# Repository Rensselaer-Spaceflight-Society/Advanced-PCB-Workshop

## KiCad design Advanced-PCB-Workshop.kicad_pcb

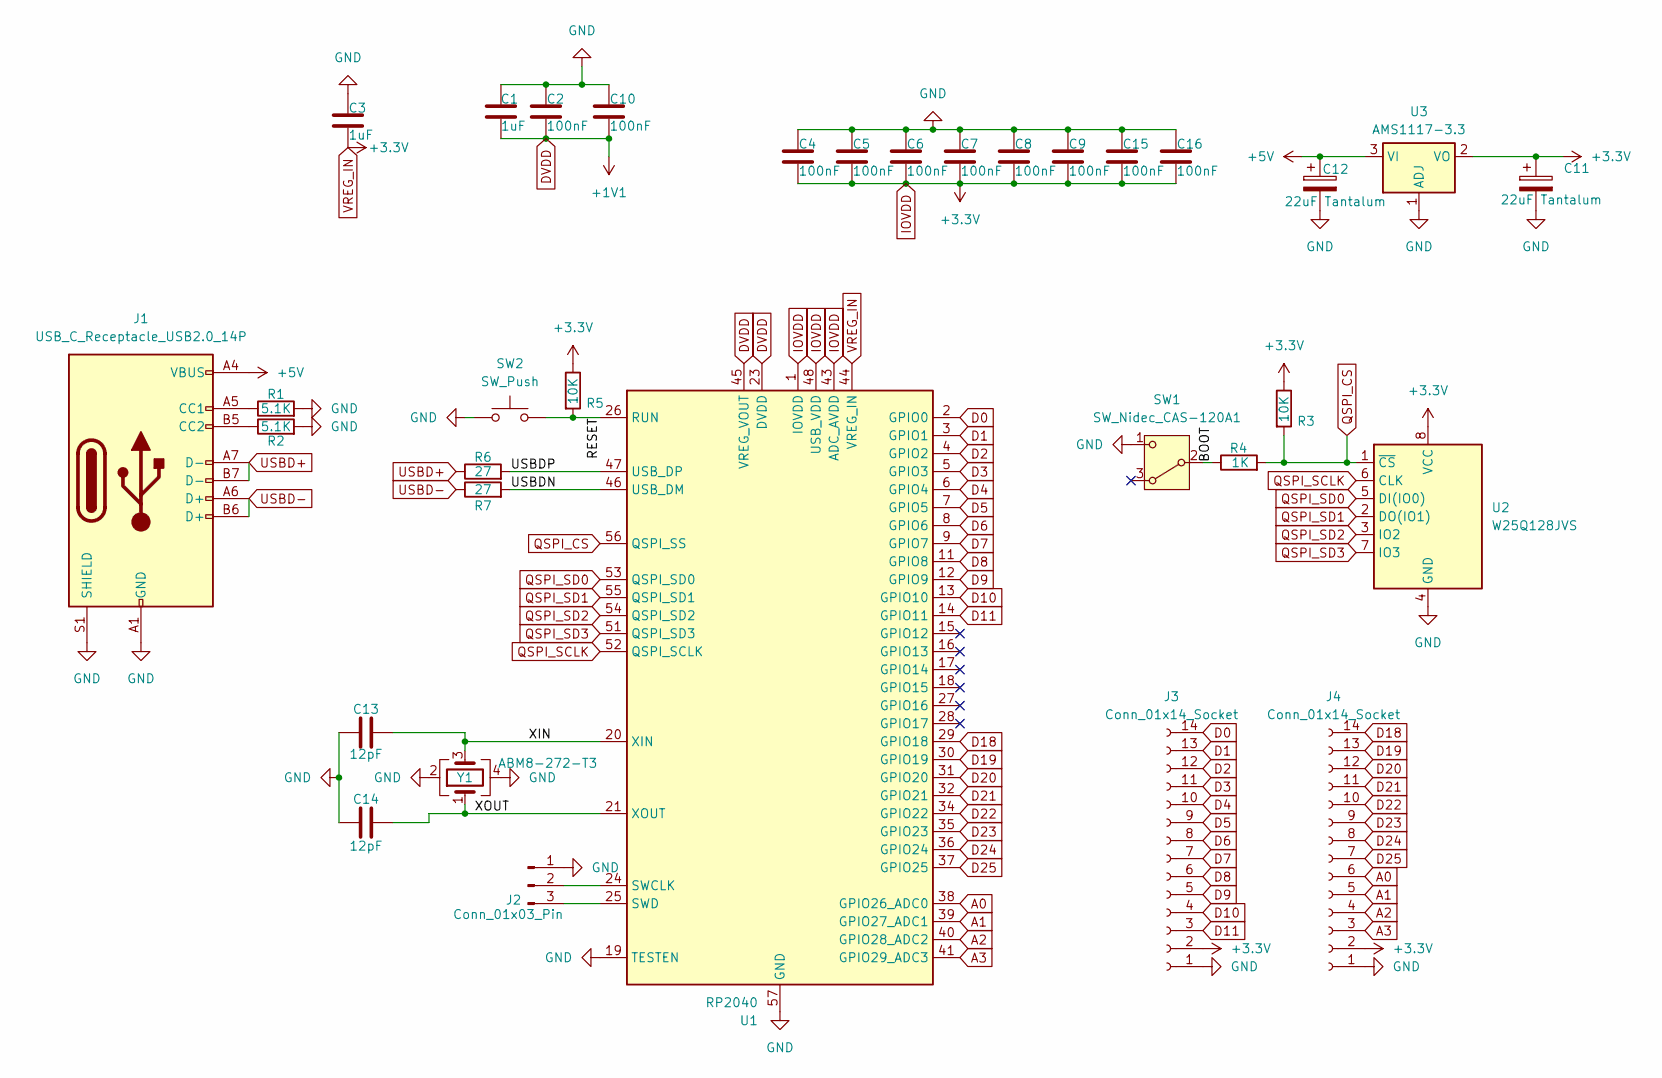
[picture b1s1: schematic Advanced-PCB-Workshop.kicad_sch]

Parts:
C1, C3: 1uF; C_0402_1005Metric
C2, C4, C5, C6, C7, C8, C9, C10, C15, C16: 100nF; C_0402_1005Metric
C11, C12: 22uF Tantalum; C_1206_3216Metric
C13, C14: 12pF; C_0402_1005Metric
J1: USB_C_Receptacle_USB2.0_14P; USB_C_Receptacle_Amphenol_12401610E4-2A
J2: Conn_01x03_Pin; PinHeader_1x03_P2.54mm_Vertical
J3, J4: Conn_01x14_Socket; PinSocket_1x14_P2.54mm_Vertical
R1, R2: 5.1K; R_0603_1608Metric_Pad0.98x0.95mm_HandSolder
R3, R5: 10K; R_0603_1608Metric_Pad0.98x0.95mm_HandSolder
R4: 1K; R_0603_1608Metric_Pad0.98x0.95mm_HandSolder
R6, R7: 27; R_0603_1608Metric_Pad0.98x0.95mm_HandSolder
SW1: SW_Nidec_CAS-120A1; Nidec_Copal_CAS-120A
SW2: SW_Push; SW_Push_1P1T_NO_CK_KMR2
U1: RP2040; QFN-56-1EP_7x7mm_P0.4mm_EP3.2x3.2mm
U2: W25Q128JVS; SOIC-8_5.3x5.3mm_P1.27mm
U3: AMS1117-3.3; SOT-223-3_TabPin2
Y1: ABM8-272-T3; Crystal_SMD_Abracon_ABM8G-4Pin_3.2x2.5mm

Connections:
+5V: C12.1, J1.A4 (VBUS), J1.A9 (VBUS), J1.B4 (VBUS), J1.B9 (VBUS), U3.3 (VI)
/BOOT: R4.1, SW1.2 (B)
/RESET: R5.2, SW2.2, U1.26 (RUN)
/USBDN: R7.2, U1.46 (USB_DM)
/USBDP: R6.2, U1.47 (USB_DP)
/XIN: C13.1, U1.20 (XIN), Y1.3
/XOUT: C14.1, U1.21 (XOUT), Y1.1
A0: J4.6, U1.38 (GPIO26_ADC0)
A1: J4.5, U1.39 (GPIO27_ADC1)
A2: J4.4, U1.40 (GPIO28_ADC2)
A3: J4.3, U1.41 (GPIO29_ADC3)
D0: J3.14, U1.2 (GPIO0)
D1: J3.13, U1.3 (GPIO1)
D2: J3.12, U1.4 (GPIO2)
D3: J3.11, U1.5 (GPIO3)
D4: J3.10, U1.6 (GPIO4)
D5: J3.9, U1.7 (GPIO5)
D6: J3.8, U1.8 (GPIO6)
D7: J3.7, U1.9 (GPIO7)
D8: J3.6, U1.11 (GPIO8)
D9: J3.5, U1.12 (GPIO9)
D10: J3.4, U1.13 (GPIO10)
D11: J3.3, U1.14 (GPIO11)
D18: J4.14, U1.29 (GPIO18)
D19: J4.13, U1.30 (GPIO19)
D20: J4.12, U1.31 (GPIO20)
D21: J4.11, U1.32 (GPIO21)
D22: J4.10, U1.34 (GPIO22)
D23: J4.9, U1.35 (GPIO23)
D24: J4.8, U1.36 (GPIO24)
D25: J4.7, U1.37 (GPIO25)
DVDD: C1.1, C2.2, C10.2, U1.23 (DVDD), U1.45 (VREG_VOUT), U1.50 (DVDD)
GND: C1.2, C2.1, C3.1, C4.1, C5.1, C6.1, C7.1, C8.1, C9.1, C10.1, C11.2, C12.2, C13.2, C14.2, C15.1, C16.1, J1.A1 (GND), J1.A12 (GND), J1.B1 (GND), J1.B12 (GND), J1.S1 (SHIELD), J2.1, J3.1, J4.1, R1.2, R2.2, SW1.1 (C), SW2.1, U1.19 (TESTEN), U1.57 (GND), U2.4 (GND), U3.1 (ADJ), Y1.2, Y1.4
IOVDD: C3.2, C4.2, C5.2, C6.2, C7.2, C8.2, C9.2, C11.1, C15.2, C16.2, J3.2, J4.2, R3.1, R5.1, U1.1 (IOVDD), U1.10 (IOVDD), U1.22 (IOVDD), U1.33 (IOVDD), U1.42 (IOVDD), U1.43 (ADC_AVDD), U1.44 (VREG_IN), U1.48 (USB_VDD), U1.49 (IOVDD), U2.8 (VCC), U3.2 (VO)
unnamed: J1.A5 (CC1), R1.1
unnamed: J1.B5 (CC2), R2.1
unnamed: J2.2, U1.24 (SWCLK)
unnamed: J2.3, U1.25 (SWD)
QSPI_CS: R3.2, R4.2, U1.56 (QSPI_SS), U2.1 (~CS)
QSPI_SCLK: U1.52 (QSPI_SCLK), U2.6 (CLK)
QSPI_SD0: U1.53 (QSPI_SD0), U2.5 (DI(IO0))
QSPI_SD1: U1.55 (QSPI_SD1), U2.2 (DO(IO1))
QSPI_SD2: U1.54 (QSPI_SD2), U2.3 (IO2)
QSPI_SD3: U1.51 (QSPI_SD3), U2.7 (IO3)
USBD+: J1.A7 (D-), J1.B7 (D-), R6.1
USBD-: J1.A6 (D+), J1.B6 (D+), R7.1

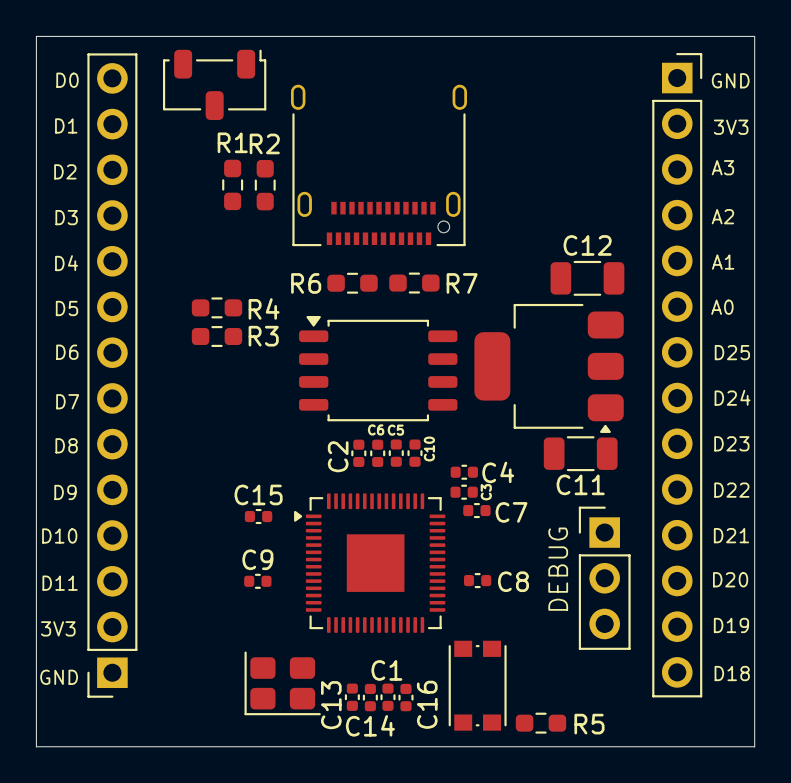
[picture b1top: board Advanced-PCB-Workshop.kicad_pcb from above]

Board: 2 copper layers, 39.9 x 39.5 mm, 33 parts (0 on the bottom side), 46 nets.

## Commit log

2025-10-21 Create Template Board
2025-10-23 Finish Template Board
2025-10-31 Completed Board
2025-10-31 Final Template
2025-11-01 Final Template v1.1
2025-11-01 Final Template v1.1.1
2025-11-01 Final Template v1.2.0
2025-11-04 Final Template v1.3.0
2025-12-18 Fully Finished Board
